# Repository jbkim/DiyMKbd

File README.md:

# Diy Mechanical Keyboard

### Hardware
- WS2812B NeoPixel: 없어도 동작함 [Link](https://www.adafruit.com/product/1655)
- 기계식 키스위치: http://www.coupang.com/vp/products/24294727

### Firmware
- MyDiyKbd: 실제 동작하는 코드
- Tets_Neopixel, Tets_Neopixel2, Test_key : 테스트용 코드

### Order
- 중국 PCB 업체 https://jlcpcb.com/

### 참고
- http://blog.komar.be/how-to-make-a-keyboard-the-matrix/
- 아두이노 Keyboard Modifiers https://www.arduino.cc/en/Reference/KeyboardModifiers
- Mac 키보드 단축키 https://support.apple.com/ko-kr/HT201236

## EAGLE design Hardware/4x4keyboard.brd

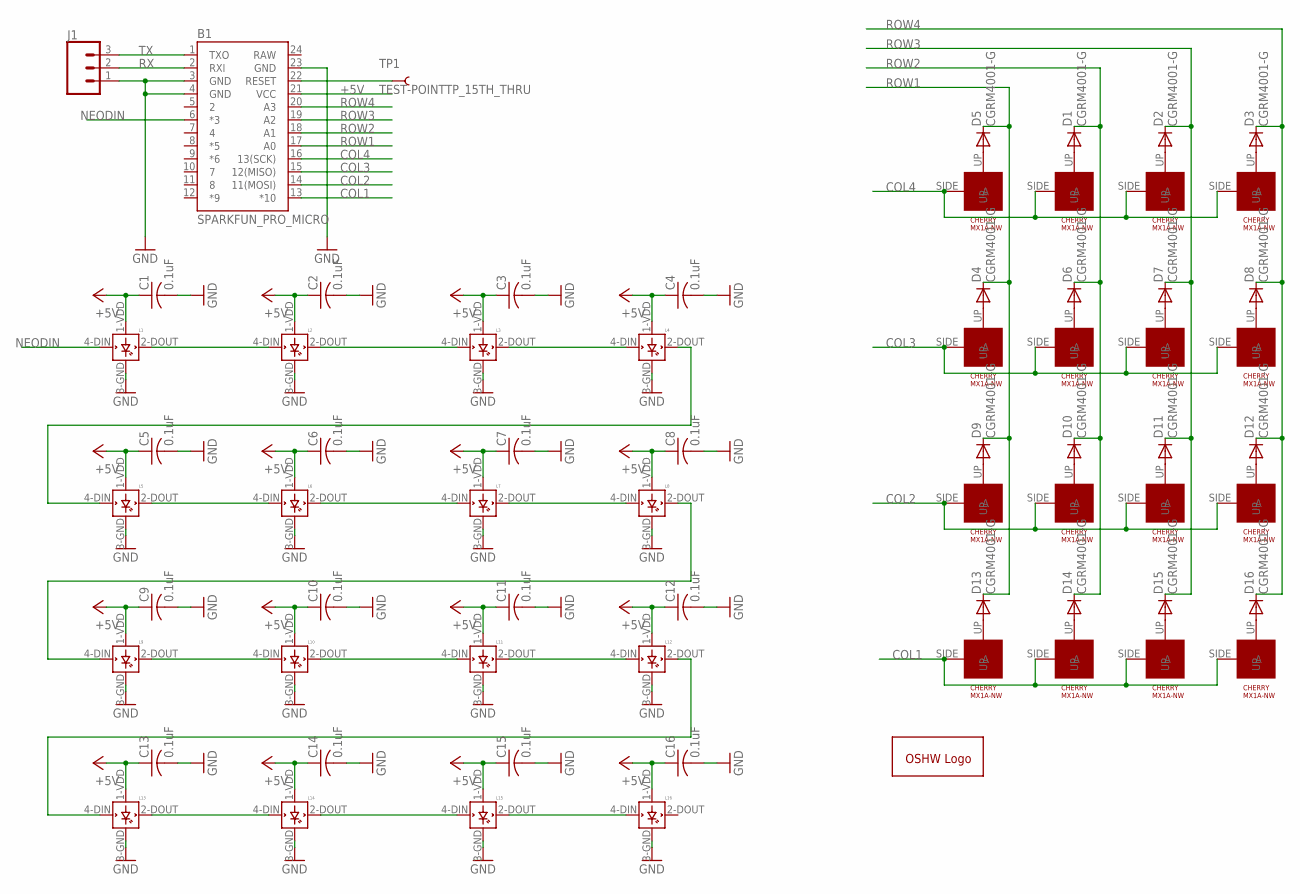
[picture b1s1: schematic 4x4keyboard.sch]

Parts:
B1: SPARKFUN_PRO_MICRO
C1, C2, C3, C4, C5, C6, C7, C8, C9, C10, C11, C12, C13, C14, C15, C16: 0.1uF; C0603
D1, D2, D3, D4, D5, D6, D7, D8, D9, D10, D11, D12, D13, D14, D15, D16: CGRM4001-G; SOD-123_MINI-SMA
GOLD_ORB_SM1: OSHWLOGOLOGO5MM; OSHW_5MM
J1: CONN_03LOCK; 1X03_LOCK
L1, L2, L3, L4, L5, L6, L7, L8, L9, L10, L11, L12, L13, L14, L15, L16: WS2812B
TP1: TEST-POINTTP_15TH_THRU; TP_15TH
U$1, U$2, U$3, U$4, U$7, U$8, U$9, U$10, U$19, U$20, U$21, U$22, U$25, U$26, U$27, U$28: CHERRY-MX1A-E1NW; CHERRYMX-NN

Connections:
+5V: B1.21 (VCC), C1.1, C2.1, C3.1, C4.1, C5.1, C6.1, C7.1, C8.1, C9.1, C10.1, C11.1, C12.1, C13.1, C14.1, C15.1, C16.1, L1.1-VDD (VDD), L2.1-VDD (VDD), L3.1-VDD (VDD), L4.1-VDD (VDD), L5.1-VDD (VDD), L6.1-VDD (VDD), L7.1-VDD (VDD), L8.1-VDD (VDD), L9.1-VDD (VDD), L10.1-VDD (VDD), L11.1-VDD (VDD), L12.1-VDD (VDD), L13.1-VDD (VDD), L14.1-VDD (VDD), L15.1-VDD (VDD), L16.1-VDD (VDD)
COL1: B1.13 (*10), U$25.SIDE (A), U$26.SIDE (A), U$27.SIDE (A), U$28.SIDE (A)
COL2: B1.14 (11(MOSI)), U$7.SIDE (A), U$8.SIDE (A), U$9.SIDE (A), U$10.SIDE (A)
COL3: B1.15 (12(MISO)), U$1.SIDE (A), U$2.SIDE (A), U$3.SIDE (A), U$4.SIDE (A)
COL4: B1.16 (13(SCK)), U$19.SIDE (A), U$20.SIDE (A), U$21.SIDE (A), U$22.SIDE (A)
GND: B1.3 (GND), B1.4 (GND), B1.23 (GND), C1.2, C2.2, C3.2, C4.2, C5.2, C6.2, C7.2, C8.2, C9.2, C10.2, C11.2, C12.2, C13.2, C14.2, C15.2, C16.2, J1.1, L1.3-GND (GND), L2.3-GND (GND), L3.3-GND (GND), L4.3-GND (GND), L5.3-GND (GND), L6.3-GND (GND), L7.3-GND (GND), L8.3-GND (GND), L9.3-GND (GND), L10.3-GND (GND), L11.3-GND (GND), L12.3-GND (GND), L13.3-GND (GND), L14.3-GND (GND), L15.3-GND (GND), L16.3-GND (GND)
unnamed: D5.A, U$19.UP
unnamed: D1.A, U$20.UP
unnamed: D2.A, U$21.UP
unnamed: D3.A, U$22.UP
unnamed: L1.2-DOUT (DOUT), L2.4-DIN (DIN)
unnamed: L2.2-DOUT (DOUT), L3.4-DIN (DIN)
unnamed: D4.A, U$2.UP
unnamed: D6.A, U$1.UP
unnamed: D7.A, U$3.UP
unnamed: D8.A, U$4.UP
unnamed: L3.2-DOUT (DOUT), L4.4-DIN (DIN)
unnamed: L4.2-DOUT (DOUT), L5.4-DIN (DIN)
unnamed: L5.2-DOUT (DOUT), L6.4-DIN (DIN)
unnamed: L6.2-DOUT (DOUT), L7.4-DIN (DIN)
unnamed: L7.2-DOUT (DOUT), L8.4-DIN (DIN)
unnamed: L8.2-DOUT (DOUT), L9.4-DIN (DIN)
unnamed: L9.2-DOUT (DOUT), L10.4-DIN (DIN)
unnamed: L10.2-DOUT (DOUT), L11.4-DIN (DIN)
unnamed: D9.A, U$7.UP
unnamed: D10.A, U$8.UP
unnamed: D11.A, U$9.UP
unnamed: D12.A, U$10.UP
unnamed: L11.2-DOUT (DOUT), L12.4-DIN (DIN)
unnamed: L12.2-DOUT (DOUT), L13.4-DIN (DIN)
unnamed: D13.A, U$25.UP
unnamed: D14.A, U$26.UP
unnamed: D15.A, U$27.UP
unnamed: D16.A, U$28.UP
unnamed: L13.2-DOUT (DOUT), L14.4-DIN (DIN)
unnamed: L14.2-DOUT (DOUT), L15.4-DIN (DIN)
unnamed: L15.2-DOUT (DOUT), L16.4-DIN (DIN)
NEODIN: B1.6 (*3), L1.4-DIN (DIN)
RAW: B1.24 (RAW)
RESET: B1.22 (RESET), TP1.P$1
ROW1: B1.17 (A0), D4.C, D5.C, D9.C, D13.C
ROW2: B1.18 (A1), D1.C, D6.C, D10.C, D14.C
ROW3: B1.19 (A2), D2.C, D7.C, D11.C, D15.C
ROW4: B1.20 (A3), D3.C, D8.C, D12.C, D16.C
RX: B1.2 (RXI), J1.2
TX: B1.1 (TXO), J1.3

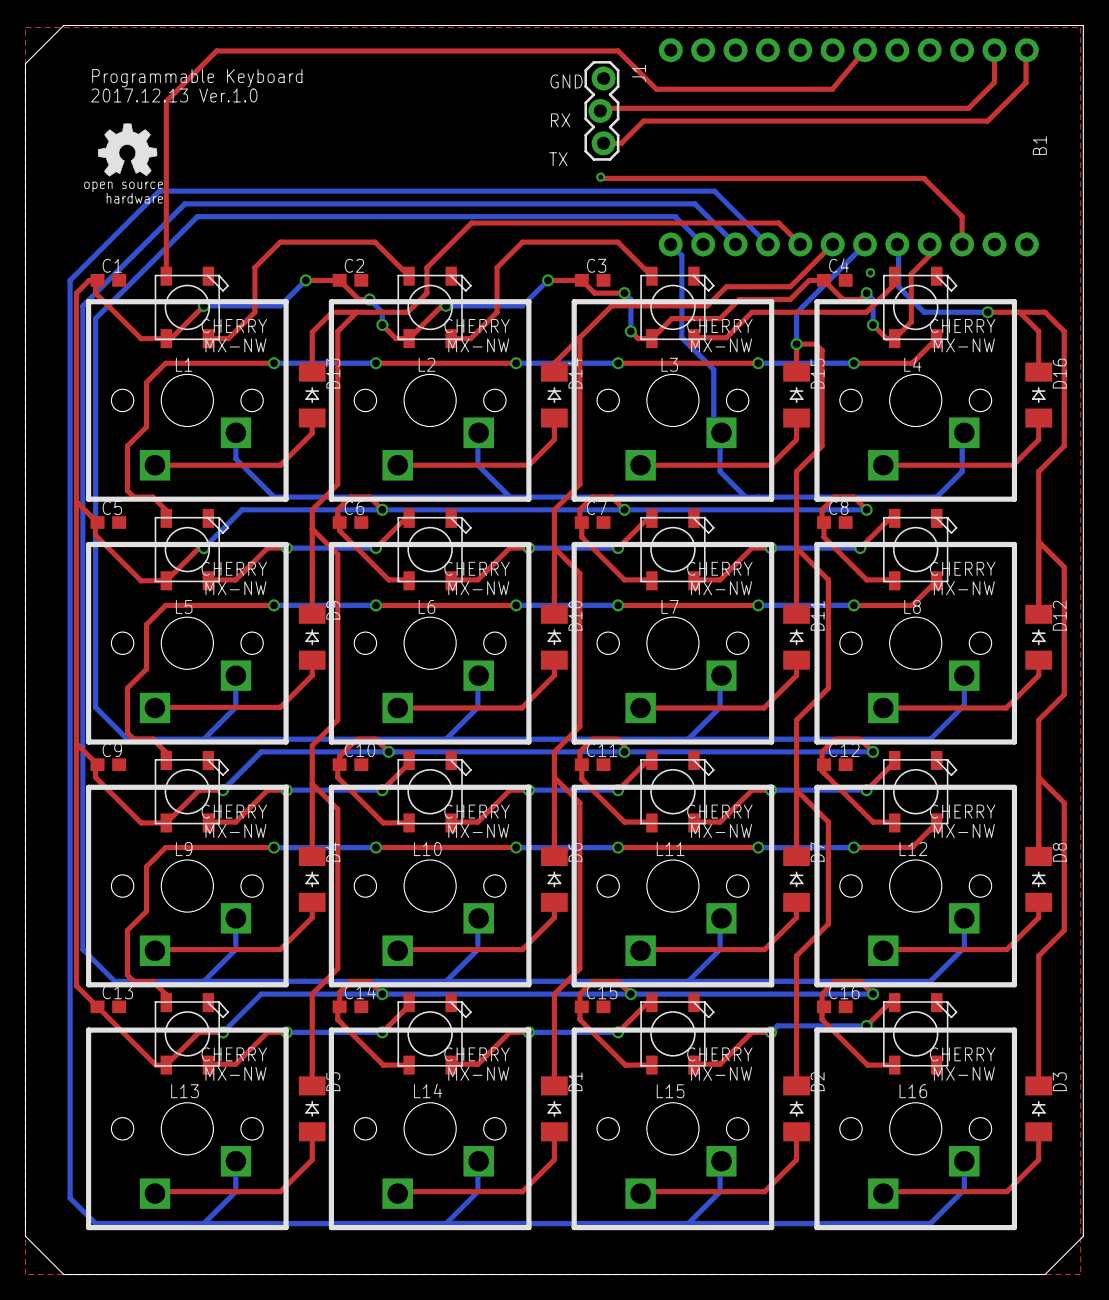
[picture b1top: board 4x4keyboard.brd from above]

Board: 2 copper layers, 83.0 x 98.0 mm, 68 parts (0 on the bottom side), 45 nets.

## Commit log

2017-12-13 add part
2017-12-15 add gerber file
2017-12-18 Add hole & rounding edge
2018-01-27 update board file
2018-01-27 Add firmware

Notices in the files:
parts and their libraries:
SparkFun-Boards: Licensing: Creative Commons ShareAlike 4.0 International - https://creativecommons.org/licenses/by-sa/4.0
